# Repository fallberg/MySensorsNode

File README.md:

# MySensorsNode
My personal [MySensors](http://mysensors.org) Node HW designs.
All designs are released under the [CERN Open Hardware Licence v1.2](http://ohwr.org/cernohl).

External dependencies:
- KiCad
- Non-standard libraries:
  - Mysensors repositories (https://github.com/mysensors-kicad)
  - Walter Lain's KiCad libraries (http://smisioto.no-ip.org/elettronica/kicad/kicad-en.htm)

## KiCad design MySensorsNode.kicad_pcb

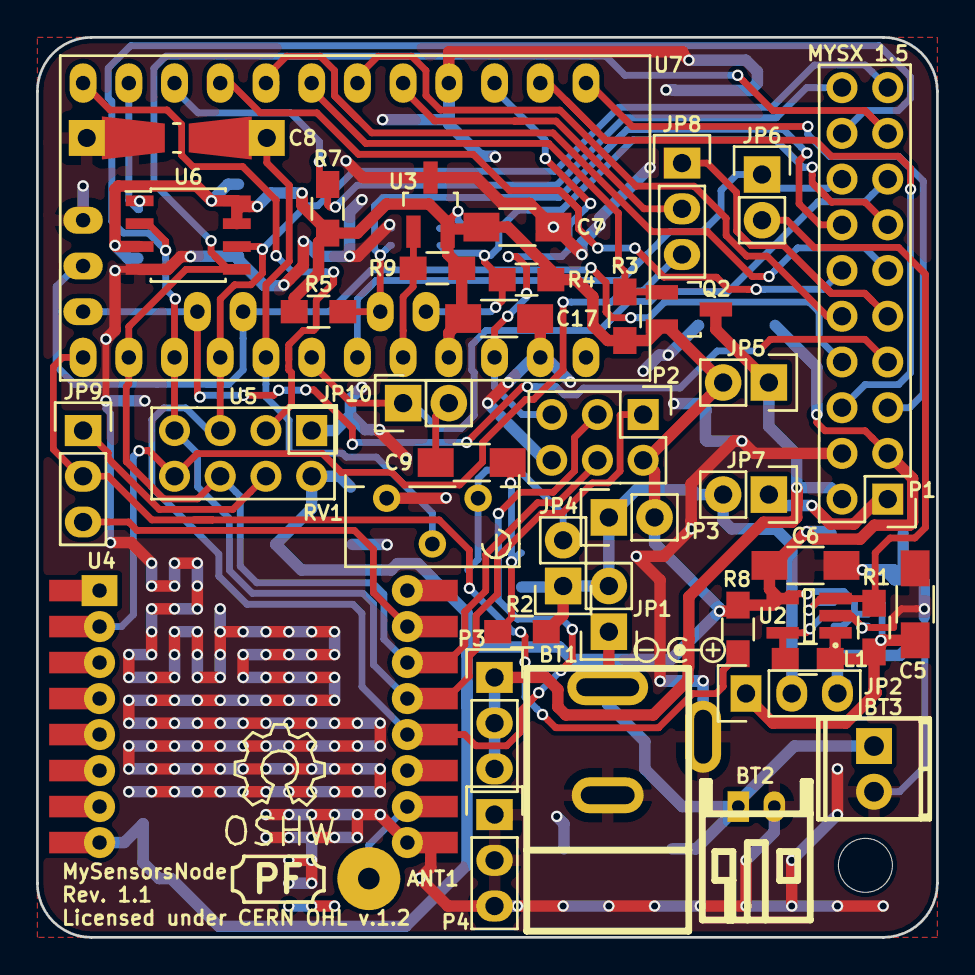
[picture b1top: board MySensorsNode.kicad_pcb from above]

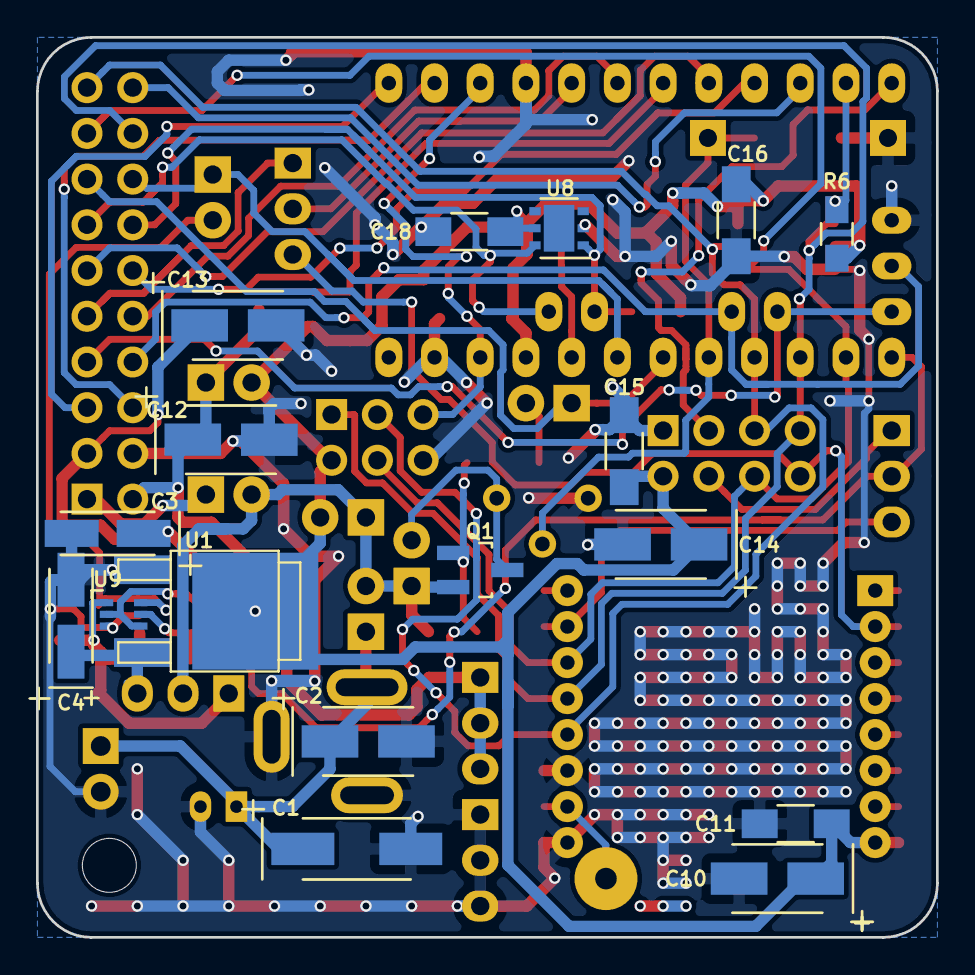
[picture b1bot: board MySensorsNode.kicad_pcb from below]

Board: 2 copper layers, 50.0 x 50.0 mm, 61 parts (17 on the bottom side), 41 nets.

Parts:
ANT1: CONN_01X01; SolderWirePad_single_1-2mmDrill
BT1: 2.5mm jack; dc_socket-kcswalter
BT2: JST; s2b-ph-kl-kcswalter
BT3: Generic; TerminalBlock2.54mmx2-kcswalter
C1: 47uF; TantalC_SizeC_EIA-6032_HandSoldering
C2, C10, C12, C13, C14: 4.7uF; TantalC_SizeB_EIA-3528_HandSoldering
C3, C4: 10uF; TantalC_SizeA_EIA-3216_HandSoldering
C5, C6: 10uF; C_1206_HandSoldering
C7, C9, C11, C15, C16, C17, C18: 0.1uF; C_1206_HandSoldering
C8: C; Resistor_SMD+THTuniversal_0805to1206_RM10_HandSoldering
HOLE1: MountingHole_3mm
JP1, JP3, JP4, JP5, JP6, JP7, JP10: Jumper_NO_Small; Pin_Header_Straight_1x02
JP2, JP8, JP9: JUMPER3; Pin_Header_Straight_1x03
L1: 4.7uH; C_0805_HandSoldering
OSHW_LOGO: Symbol_OSHW-Logo_SilkScreen
P1: MYSX_1.5
P2: CONN_02X03; Pin_Header_Straight_2x03
P3, P4: CONN_01X03; Pin_Header_Straight_1x03
PLUG_SPEC: LOGO; Logo_silk_polarity_center_5x1.4mm
Q1, Q2: DMP3056L-7; SOT-23_Handsoldering
R1: 150K; R_0805_HandSoldering
R2, R3, R4, R5: 10K; R_0805_HandSoldering
R6, R7, R8, R9: 56K; R_0805_HandSoldering
RV1: 1M; Potentiometer_Bourns_3296Y_3-8Zoll_Angular_ScrewUp
U1: LD1117DT33TR; d-pak-kcswalter
U2: TPS61097A; SOT-23-5_Handsoldering
U3: ATSHA204A; SOT-23_Handsoldering
U4: RFM69HW; RFM69HW_SMD_ThroughHole_Handsoldering
U5: NRF24L01
U6: AT25DF512C; SOIC-8_3.9x4.9mm_Pitch1.27mm
U7: ArduinoProMini; pro_mini
U8: Si7021; DFN-6-1EP_3x3mm_Pitch0.95mm
U9: TPS61221; SC-70-6

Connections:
+3.3VP: C12.1, JP5.1, P1.2, P3.1, P3.2, P3.3, Q2.3
+3V3: C3.1, C6.1, C7.1, C10.1, C11.2, C13.1, C14.1, C15.2, C16.2, C17.1, C18.1, JP3.2, JP5.2, P1.3, P2.2, Q2.2, R3.2, R4.2, R5.2, R6.2, R7.2, R8.1, R9.2, U1.2, U2.4, U3.2, U4.8, U5.2, U6.3, U6.7, U6.8, U7.21, U8.5, U9.2, U9.4
+BATT: JP1.2, JP2.2, JP3.1, JP4.1, JP7.2, Q1.2, R2.2
/MISO: P1.18, P2.1, U4.13, U5.7, U6.2, U7.15
/MOSI: P1.17, P2.4, U4.14, U5.6, U6.5, U7.14
/SCK: P1.19, P2.3, U4.12, U5.5, U6.6, U7.16
ATSHA_SDA: R9.1, U3.1, U7.20
FLASH_CSN: R6.1, U6.1, U7.11
GND: BT1.1, BT1.2, BT2.2, BT3.2, C1.2, C2.2, C3.2, C4.2, C5.2, C6.2, C7.2, C8.2, C10.2, C11.1, C12.2, C13.2, C14.2, C15.1, C16.1, C17.2, C18.2, P1.4, P2.6, P4.1, P4.2, P4.3, RV1.3, U1.1, U2.2, U3.3, U4.9, U4.11, U5.1, U6.4, U7.4, U7.23, U7.29, U8.2, U9.3
MYSX_3.3V_EN: Q2.1, R3.1, U7.7
MYSX_A1: P1.7, U7.27
MYSX_A2: P1.8, U7.28
MYSX_D1_DFM: P1.5, U7.1
MYSX_D2_DTM: P1.6, U7.2
MYSX_D3_INT: JP8.1, P1.9
MYSX_D4_INT: P1.10, U7.6
MYSX_D5_PWM: P1.11, U7.8
MYSX_D6_PWM: P1.12, U7.9
MYSX_D7_SCL: P1.13, R4.1, U7.26, U8.6
MYSX_D8_SDA: P1.14, R5.1, U7.25, U8.1
MYSX_D9_A3: JP10.1, P1.15, U7.18
MYSX_D10_A4: JP6.1, P1.16, U7.19
MYSX_D14_CS: P1.20, R7.1, U7.10
unnamed: ANT1.1, U4.10
unnamed: BT1.3, BT2.1, BT3.1, C1.1, C2.1, JP1.1
unnamed: C4.1, JP2.3, U1.3
unnamed: C5.1, JP2.1, L1.2, R1.1, U2.1, U9.1
unnamed: C9.1, JP10.2
unnamed: C9.2, Q1.1, R2.1
unnamed: JP4.2, Q1.3, RV1.1
unnamed: JP6.2, R1.2, U2.3, U9.6
unnamed: JP7.1, P1.1
unnamed: JP8.2, U7.5
unnamed: JP9.2, R8.2, U7.13
unnamed: L1.1, U2.5, U9.5
RESET: P2.5, U7.3, U7.22
RF24_CE: U5.3, U7.12
RF24_CSN: JP9.1, U5.4
RF69_NSS: JP9.3, U4.15
RF_INT: JP8.3, U4.2, U5.8
VBAT_SMPL: C8.1, RV1.2, U7.17

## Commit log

2015-06-06 Added .gitignore to filter autogenerated backups
2015-06-10 Added CERN Open Hardware Licence v1.2 license text
2015-06-23 Update README with dependencies
2015-06-25 First version of my generic MySensors node
    Features:
    - Switchable battery level measurement
    - By-passable 3.3V step-up regulator
    - Possibility to disable sensor power rail
    - Optional additional 5V step-up regulator for sensors
    - 2.5mm DC jack power supply footprint
2015-08-21 Rev. 1.1 of my generic MySensors node
    * Added resistor to terminate REG_BYPASS to default 'on' (fixes #2)
    * Added extra RF bypass capacitors (fixes #5)
    * Updated RF69 footprint to have sligtly wider space between holes
    * Added optional pull-ups to CS signals on SPI devices (fixes #3)
    * Reversed polarity of CON1 to fit battery default pinout (fixes #1)
    * Sensor pin connector swapped in favor of MYSX 1.5 connector
2015-08-24 Updated .gitignore to filter some autogenerated files
2015-08-24 Minor beautifications and updated CHANGES.txt
2015-08-24 Updated U1 footprint
    U1 footprint is now available in the mysensors-kicad repository
2015-08-27 Created 5x5 cm layout
    BT4 and BT5 are omitted in this layout.
    Fixes #7.
2015-08-27 Radio module footprints updated to latest revisions
2015-08-31 Adjusted track width of some power-nets
2015-08-31 Created layout for LE-BOX-0028
    Fixes #8
2015-08-31 Moved BT5 to make more room for mounting screw
2015-09-01 Added a step-up reg and some sourcing details
    Added TI TPS61221 (3.3V fixed) as an alternative to TPS61097A.
    Also added some more sourcing details to some components in the
    schematic.
2015-09-10 Added more sourcing details
    Also minor schematic beautifications
2015-09-12 Updated CR123 battery holder footprint
    Fixes #11
2015-09-12 Completed sourcing details of all components
    Sourcing data is organized in the following way:
    Supplier1 - The primary supplier (also the cheapest)
    Supplier1 part - The primary supplier part number
    Supplier1 link - Link to the part on the suppliers homepage
    The same goes for Supplier2 to 5.
    All parts also have a Vendor and Vendor part field to identify
2015-09-12 Created a BOM generator script for this project
    The BOM generator (verified on KiCad for Linux) parses the netllist
    data and outputs 9 BOM files:
    MySensorsNode_Full.txt - Full BOM with all suppliers
    MySensorsNode_Cheapest.txt - BOM with the cheapest supplier
    MySensorsNode_AliExpress.txt - BOM with all parts available from AliExpress
    MySensorsNode_Digi-Key.txt - BOM with all parts available from Digi-Key
2015-09-12 Created BOM(s)
    Fixes #10
2015-09-12 Minor layout beautifications
2015-09-12 Created manufacturing outputs
    Also created DirtyPCBs-formatted archives.
    Fixes #9
2015-09-12 Removed origin-symbol from board outlines
2015-09-13 Corrected Mouser/Farnell parts for P2
2015-09-14 Updated CHANGES.txt with git log
2016-04-11 Adjusted 3d model search paths

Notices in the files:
MySensorsNode.kicad_pcb:
Copyright (c) 2015 Patrick Fallberg
Licensed under CERN OHL v.1.2
